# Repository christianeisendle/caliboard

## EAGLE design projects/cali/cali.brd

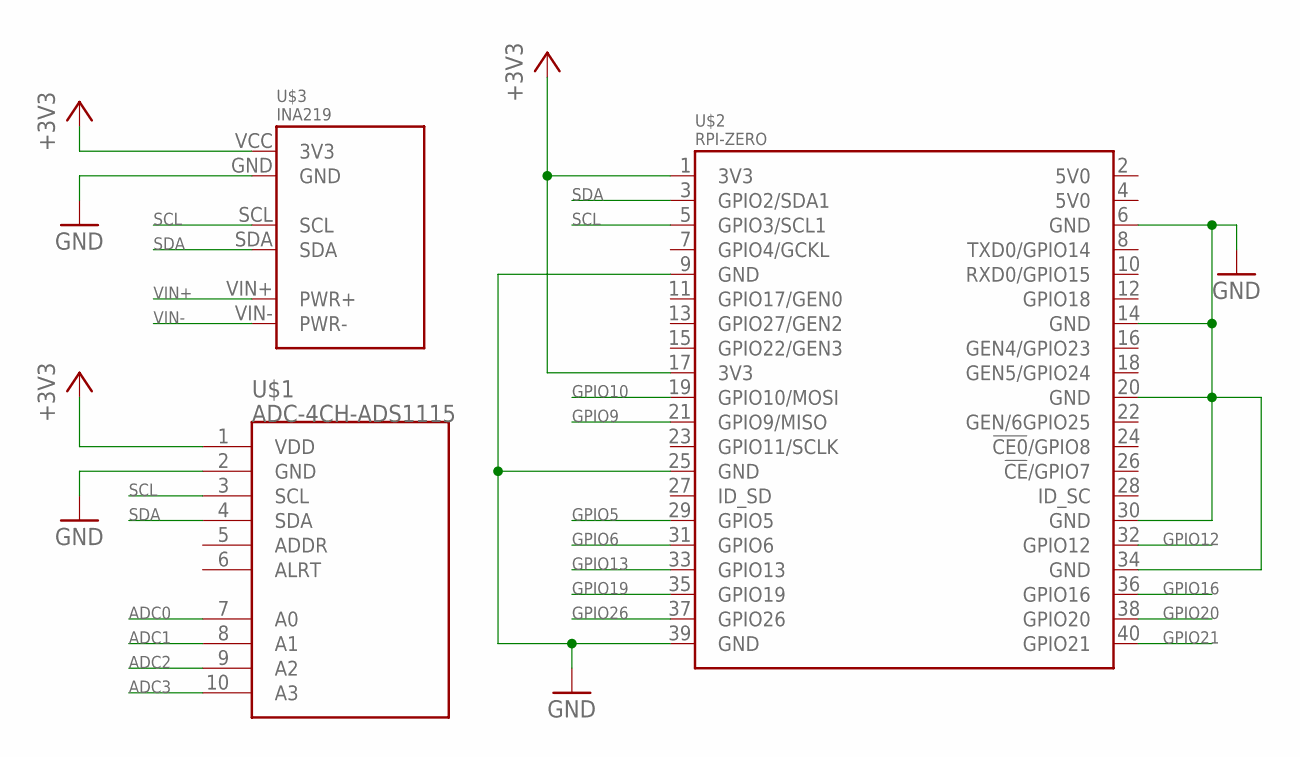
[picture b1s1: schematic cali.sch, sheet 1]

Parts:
U$1: ADC-4CH-ADS1115
U$2: RPI-ZERO; RASP_PI_ZERO_BOARD_FULL
U$3: INA219

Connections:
+3V3: U$1.1 (VDD), U$2.1 (3V3), U$2.17 (3V3), U$3.VCC (3V3); also elsewhere on the board
ADC0: U$1.7 (A0); also elsewhere on the board
ADC1: U$1.8 (A1); also elsewhere on the board
ADC2: U$1.9 (A2); also elsewhere on the board
ADC3: U$1.10 (A3); also elsewhere on the board
GND: U$1.2 (GND), U$2.6 (GND), U$2.9 (GND), U$2.14 (GND), U$2.20 (GND), U$2.25 (GND), U$2.30 (GND), U$2.34 (GND), U$2.39 (GND), U$3.GND; also elsewhere on the board
GPIO5: U$2.29 (GPIO5); also elsewhere on the board
GPIO6: U$2.31 (GPIO6); also elsewhere on the board
GPIO9: U$2.21 (GPIO9/MISO); also elsewhere on the board
GPIO10: U$2.19 (GPIO10/MOSI)
GPIO12: U$2.32 (GPIO12)
GPIO13: U$2.33 (GPIO13); also elsewhere on the board
GPIO16: U$2.36 (GPIO16)
GPIO19: U$2.35 (GPIO19); also elsewhere on the board
GPIO20: U$2.38 (GPIO20)
GPIO21: U$2.40 (GPIO21)
GPIO26: U$2.37 (GPIO26); also elsewhere on the board
SCL: U$1.3 (SCL), U$2.5 (GPIO3/SCL1), U$3.SCL
SDA: U$1.4 (SDA), U$2.3 (GPIO2/SDA1), U$3.SDA
VIN+: U$3.VIN+ (PWR+)
VIN-: U$3.VIN- (PWR-)

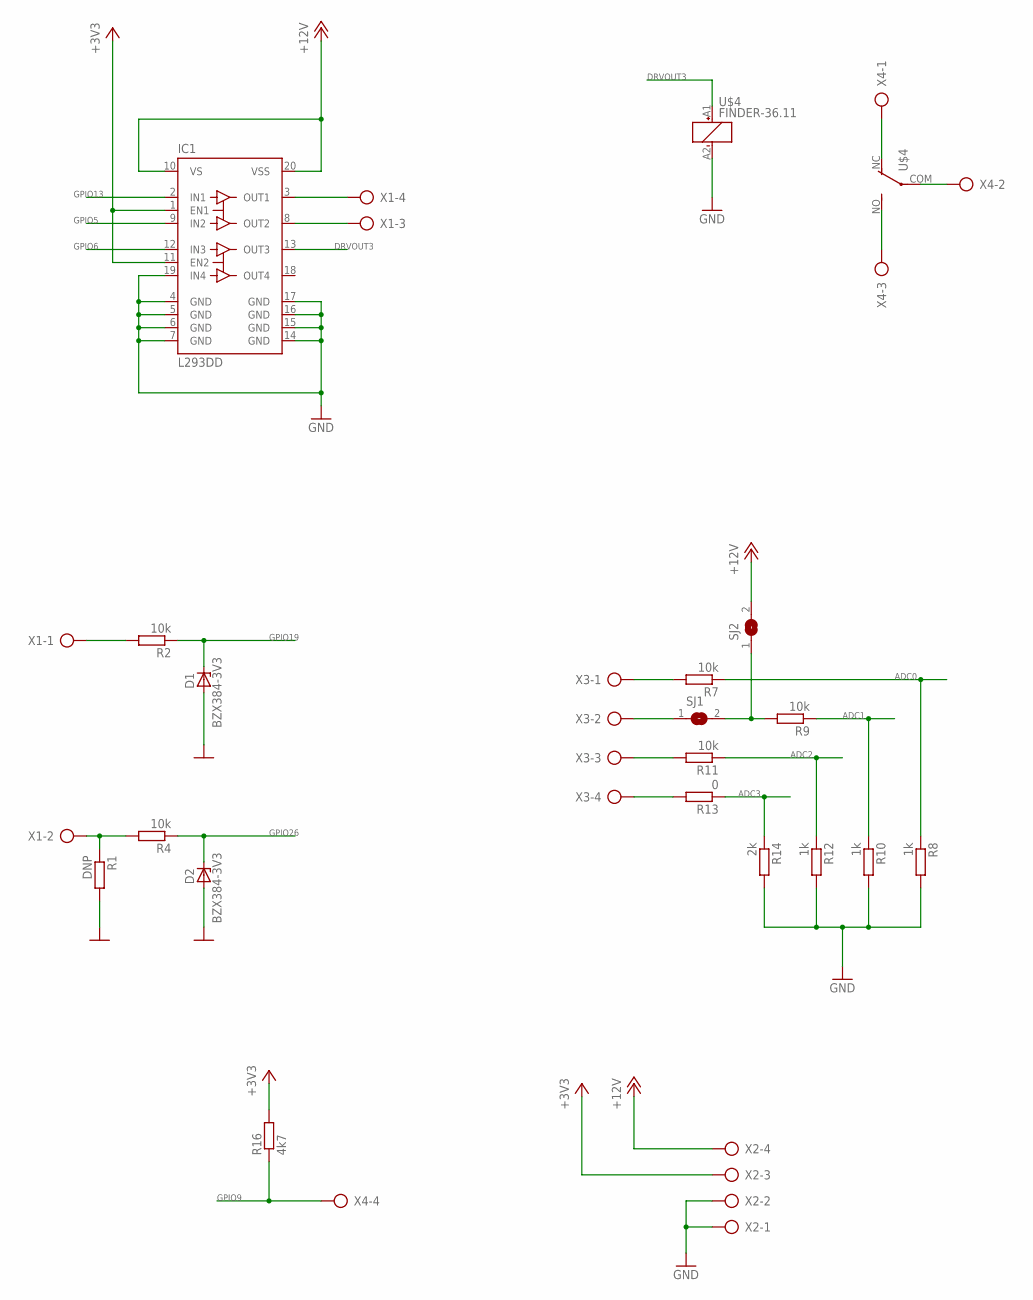
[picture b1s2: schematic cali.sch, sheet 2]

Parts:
D1, D2: BZX384-3V3; SOD323(F)
IC1: L293DD; SO20
R1: DNP; R1206
R2, R4, R7, R9, R11: 10k; R1206
R8, R10, R12: 1k; R1206
R13: 0; R1206
R14: 2k; R1206
R16: 4k7; R1206
SJ1, SJ2: SJ
U$4: FINDER-36.11
X1, X2, X3, X4: AK500/4

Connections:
+3V3: IC1.1 (EN1), IC1.11 (EN2), R16.2, X2.3; also elsewhere on the board
+12V: IC1.10 (VS), IC1.20 (VSS), SJ2.2, X2.4
ADC0: R7.1, R8.1; also elsewhere on the board
ADC1: R9.1, R10.1; also elsewhere on the board
ADC2: R11.1, R12.1; also elsewhere on the board
ADC3: R13.1, R14.1; also elsewhere on the board
DRVOUT3: IC1.13 (OUT3), U$4.A1 (+)
GND: D1.2 (A), D2.2 (A), IC1.4 (GND), IC1.5 (GND), IC1.6 (GND), IC1.7 (GND), IC1.14 (GND), IC1.15 (GND), IC1.16 (GND), IC1.17 (GND), IC1.19 (IN4), R1.2, R8.2, R10.2, R12.2, R14.2, U$4.A2 (-), X2.1, X2.2; also elsewhere on the board
GPIO5: IC1.9 (IN2); also elsewhere on the board
GPIO6: IC1.12 (IN3); also elsewhere on the board
GPIO9: R16.1, X4.4; also elsewhere on the board
GPIO13: IC1.2 (IN1); also elsewhere on the board
GPIO19: D1.1 (C), R2.1; also elsewhere on the board
GPIO26: D2.1 (C), R4.1; also elsewhere on the board
I_SOL: R13.2, X3.4
unnamed: R2.2, X1.1
unnamed: IC1.3 (OUT1), X1.4
unnamed: U$4.NO (S), X4.3
unnamed: U$4.COM, X4.2
unnamed: IC1.8 (OUT2), X1.3
unnamed: U$4.NC (O), X4.1
unnamed: R1.1, R4.2, X1.2
unnamed: R9.2, SJ1.2, SJ2.1
V_BAT: SJ1.1, X3.2
V_SOL: R7.2, X3.1
V_START: R11.2, X3.3

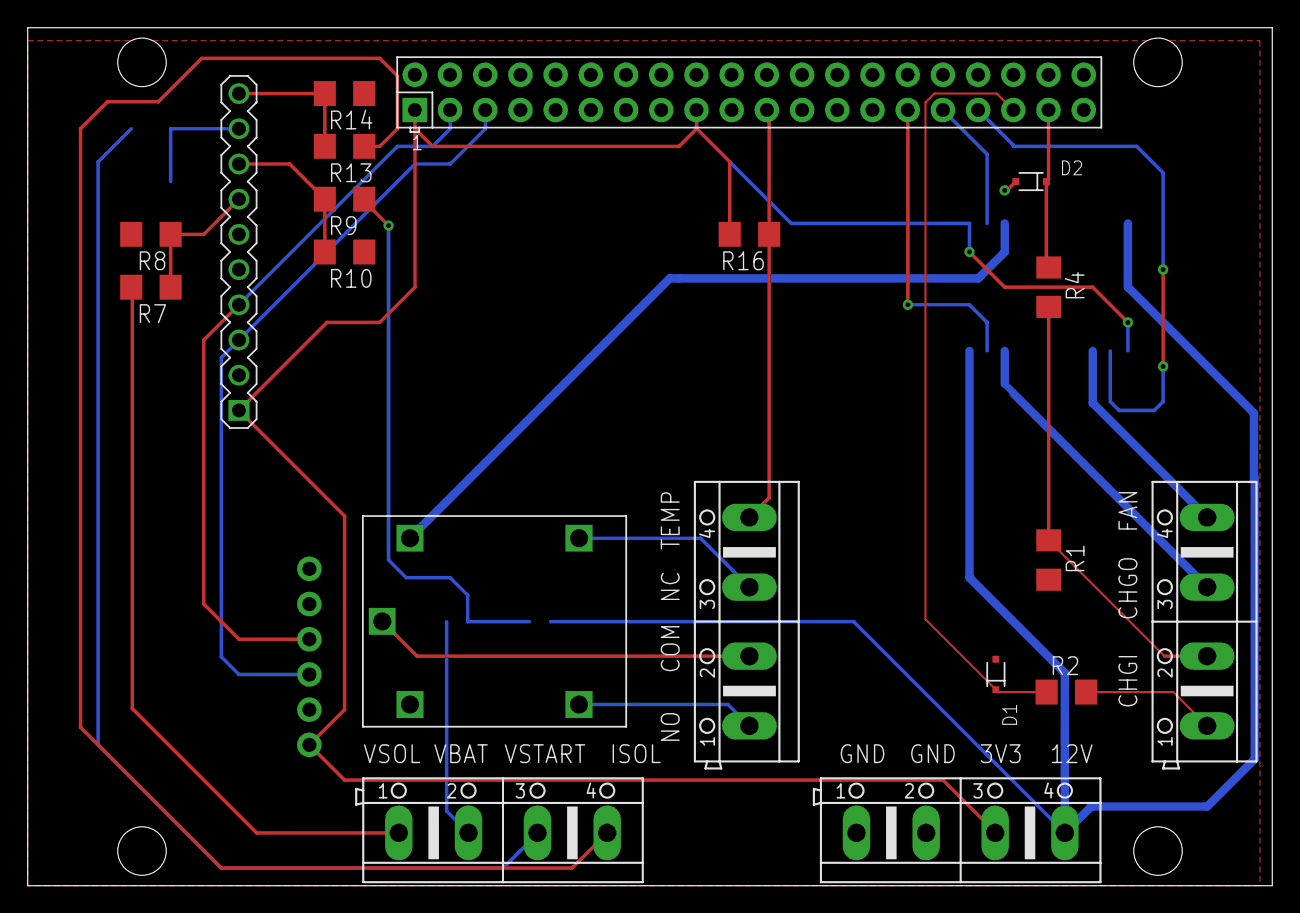
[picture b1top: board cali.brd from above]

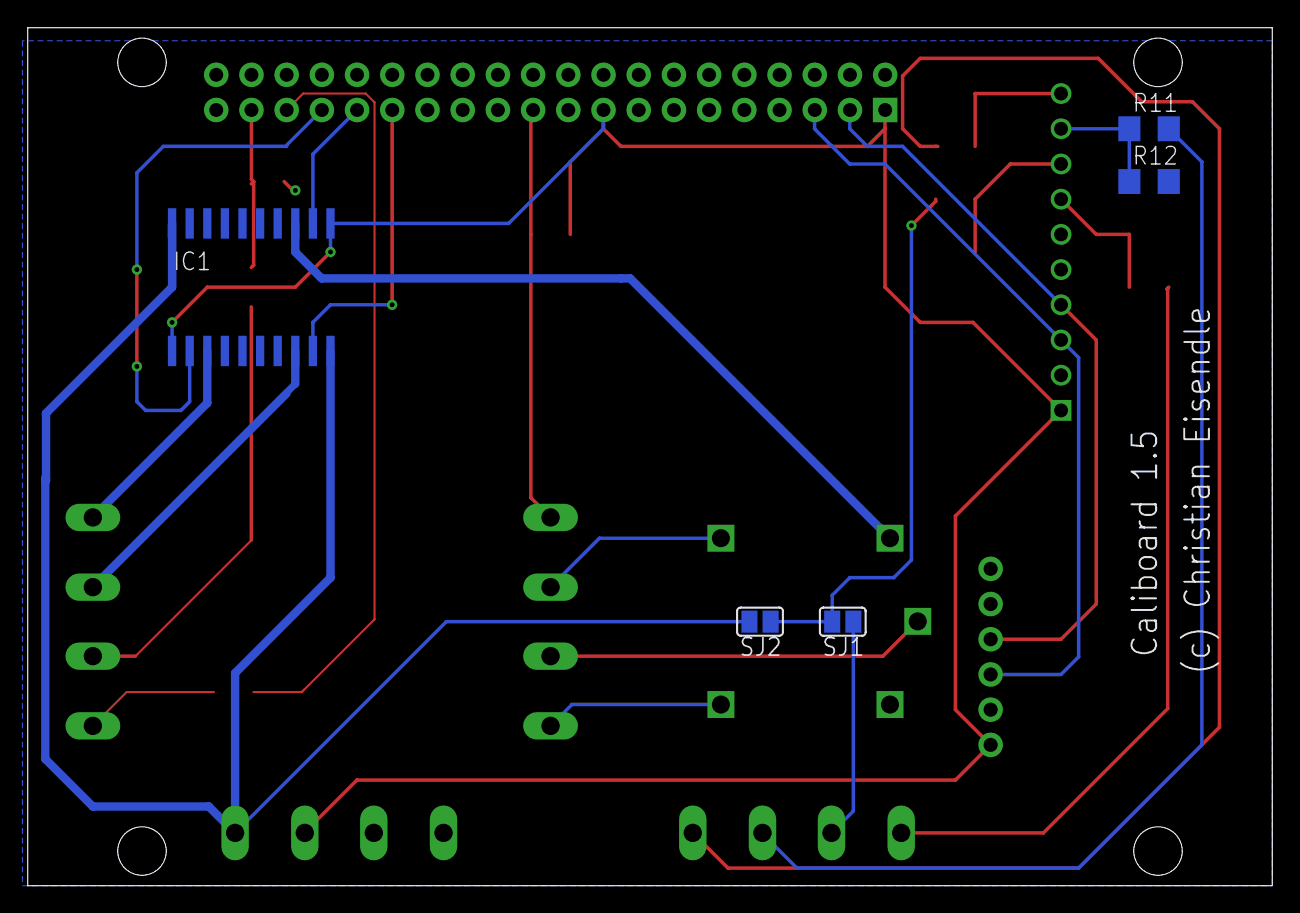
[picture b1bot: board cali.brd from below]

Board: 2 copper layers, 89.8 x 61.9 mm, 25 parts (5 on the bottom side), 28 nets.

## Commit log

2019-09-17 Add transistor library for IRLML2502
2019-09-17 Add transistor library for 2N7002
2019-09-17 Duplicating relay library to add new relay
2019-09-17 Add Finder 36.11 relay
2019-09-17 Board v1.0
2019-09-18 Caliboard 1.0 routing done
2019-09-18 Caliboard 1.0, avoid cutting bottom layer ground plane
2019-09-24 Caliboard v1.1
    - Change GPIOs to use GPIO of first row only
    - Modify level shifter to sustain 12V
    - Change GPIO for PWM
2019-09-25 Change board dimension layer for INA219 and ADS1115 from tPlace to HELP to avoid printing on silkscreen
2019-09-25 Board file update after change of libs
2019-09-25 Add cam file for generating 2 layer PCB gerber files
2019-10-07 Caliboard 1.2
    - Fan output now has a PP stage
    - Temp-sensor 4k7 pull up
2019-10-15 Caliboard 1.4
2022-08-21 Add additional 12V input

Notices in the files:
parts and their libraries:
diy-modules: Released under the Creative Commons Attribution 4.0 International License: http://creativecommons.org/licenses/by/4.0
